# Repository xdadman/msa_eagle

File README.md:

#MSA - Scotty's Modular Spectrum Analyzer Eagle Schematics and PCB Layouts
This repository contains Eagle schematics and PCB layouts for Scotty's MSA.

See http://scottyspectrumanalyzer.com/ website for detailed information how to build, calibrate, and operate the MSA. 

The files and in Eagle 7.1 format.

Most of the parts in the MSA library have defined Farnell order codes.
The rest are from Digikey and Minicircuits.

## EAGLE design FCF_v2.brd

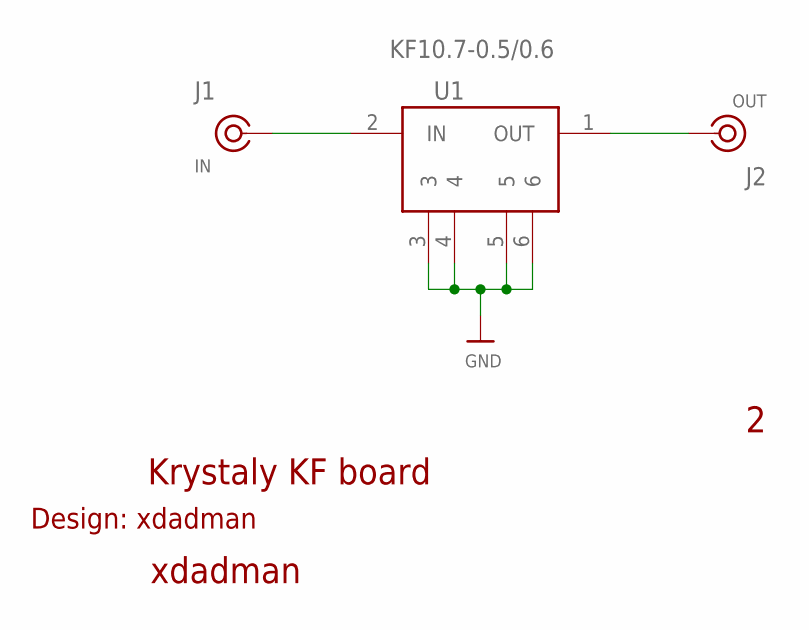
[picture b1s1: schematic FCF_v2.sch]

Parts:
J1: IN; SLIM_COAX_PAD
J2: OUT; SLIM_COAX_PAD
U1: KF10.7-0.5/0.6; KF-17

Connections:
GND: J1.GND, J2.GND, U1.3, U1.4, U1.5, U1.6
unnamed: J1.SIG (1), U1.2 (IN)
unnamed: J2.SIG (1), U1.1 (OUT)

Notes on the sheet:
xdadman
Krystaly KF board
Design: xdadman

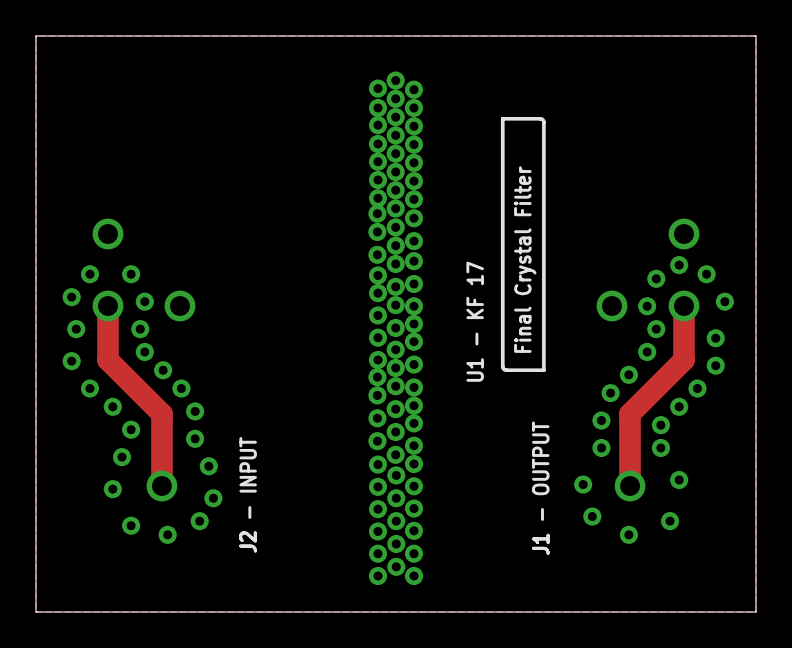
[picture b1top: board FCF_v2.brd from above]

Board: 2 copper layers, 40.0 x 32.0 mm, 3 parts (1 on the bottom side), 3 nets.

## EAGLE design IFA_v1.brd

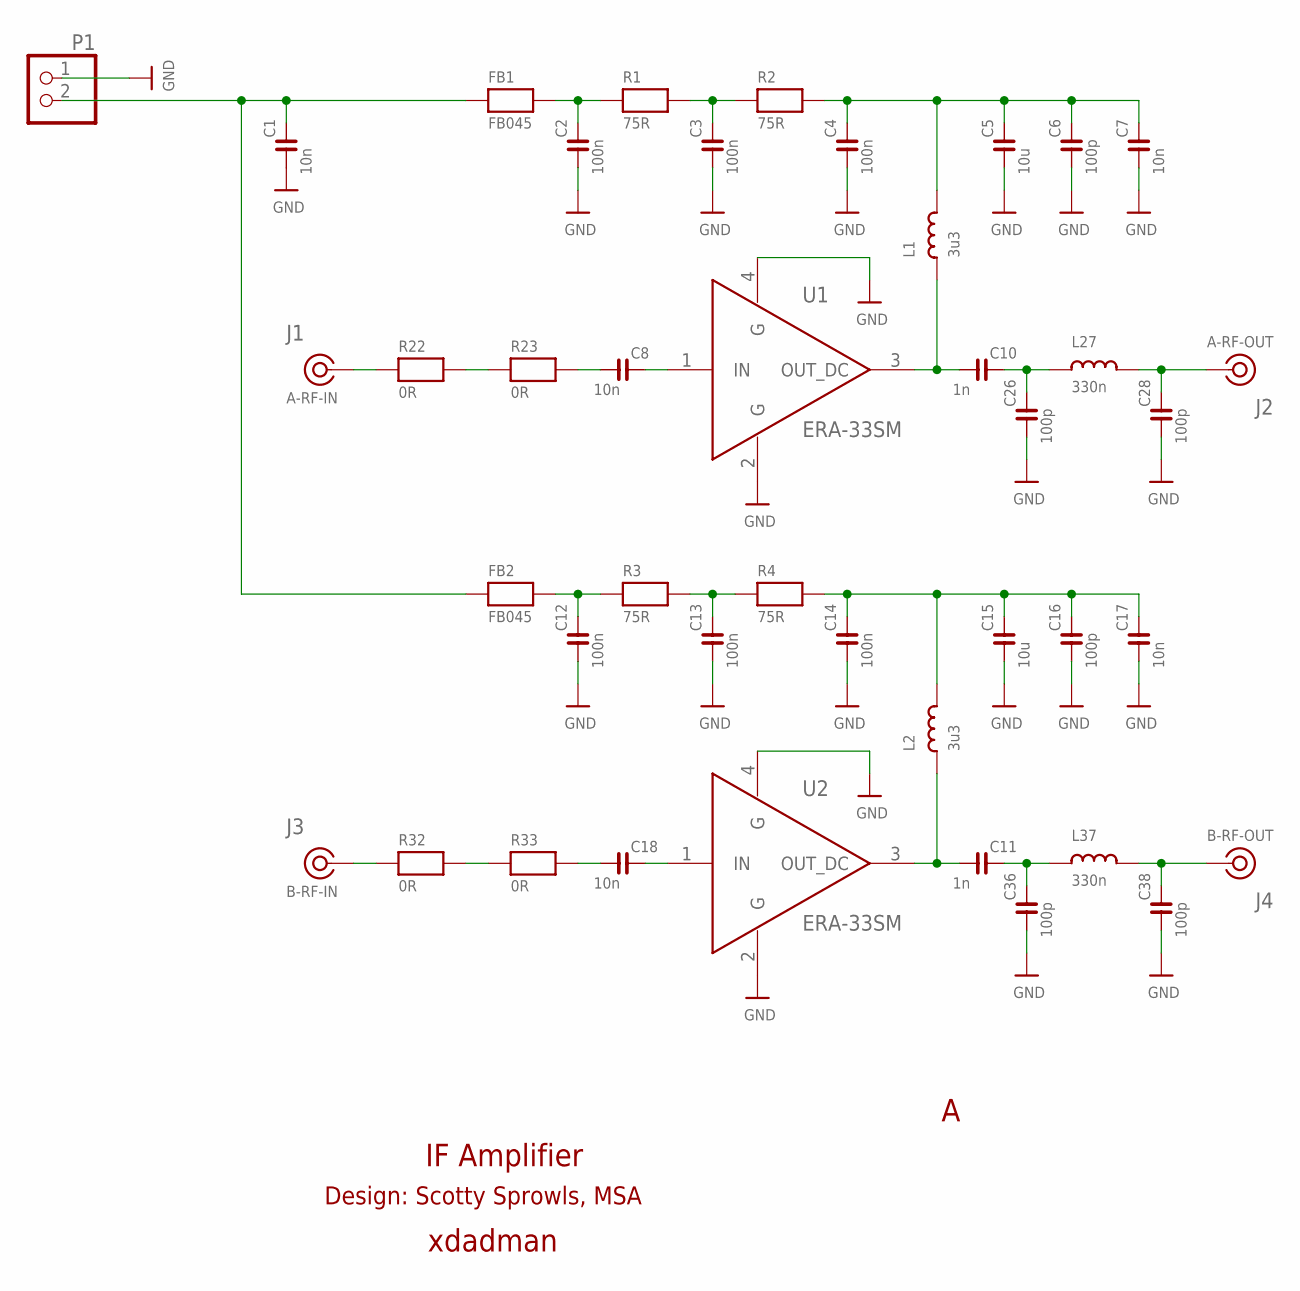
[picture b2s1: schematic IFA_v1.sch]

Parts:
C1, C7, C8, C17, C18: 10n; C0805
C2, C3, C4, C12, C13, C14: 100n; C0805
C5, C15: 10u; C1206
C6, C16, C26, C28, C36, C38: 100p; C0805
C10, C11: 1n; C0805
FB1, FB2: FB045; R0805
J1: A-RF-IN; SLIM_COAX_PAD
J2: A-RF-OUT; SLIM_COAX_PAD
J3: B-RF-IN; SLIM_COAX_PAD
J4: B-RF-OUT; SLIM_COAX_PAD
L1, L2: 3u3; L805
L27, L37: 330n; L805
P1: PINHD-1X2; 1X02
R1, R2, R3, R4: 75R; R0805
R22, R23, R32, R33: 0R; R0805
U1, U2: ERA-33SM; WW107

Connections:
GND: C1.1, C2.1, C3.1, C4.1, C5.1, C6.1, C7.1, C12.1, C13.1, C14.1, C15.1, C16.1, C17.1, C26.1, C28.1, C36.1, C38.1, J1.GND, J2.GND, J3.GND, J4.GND, P1.1, U1.2 (G), U1.4 (G), U2.2 (G), U2.4 (G)
unnamed: C2.2, FB1.2, R1.1
unnamed: C1.2, FB1.1, FB2.1, P1.2
unnamed: C3.2, R1.2, R2.1
unnamed: J1.SIG (1), R22.1
unnamed: C4.2, C5.2, C6.2, C7.2, L1.2, R2.2
unnamed: R22.2, R23.1
unnamed: C8.1, R23.2
unnamed: C8.2, U1.1 (IN)
unnamed: C28.2, J2.SIG (1), L27.2
unnamed: C10.1, L1.1, U1.3 (OUT_DC)
unnamed: C10.2, C26.2, L27.1
unnamed: C12.2, FB2.2, R3.1
unnamed: C13.2, R3.2, R4.1
unnamed: C14.2, C15.2, C16.2, C17.2, L2.2, R4.2
unnamed: J3.SIG (1), R32.1
unnamed: R32.2, R33.1
unnamed: C18.1, R33.2
unnamed: C18.2, U2.1 (IN)
unnamed: C11.1, L2.1, U2.3 (OUT_DC)
unnamed: C11.2, C36.2, L37.1
unnamed: C38.2, J4.SIG (1), L37.2

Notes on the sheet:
xdadman
IF Amplifier
Design: Scotty Sprowls, MSA

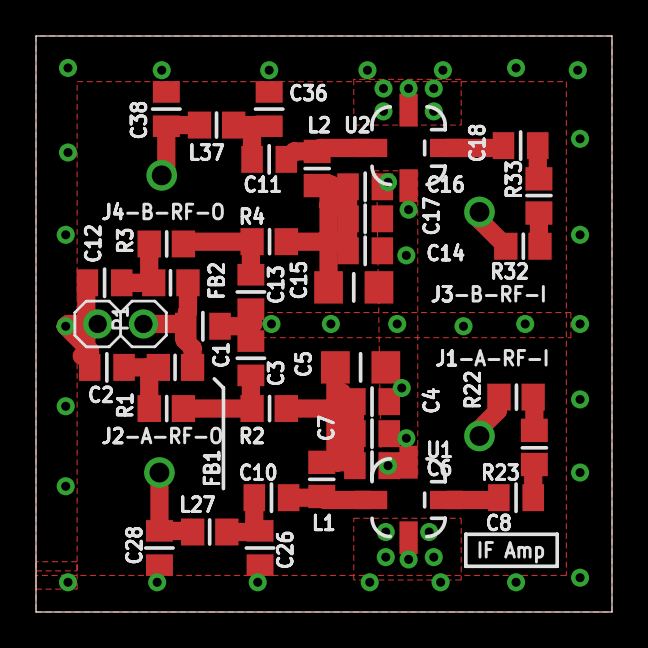
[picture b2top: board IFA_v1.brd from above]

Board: 2 copper layers, 32.0 x 32.0 mm, 42 parts (0 on the bottom side), 22 nets.

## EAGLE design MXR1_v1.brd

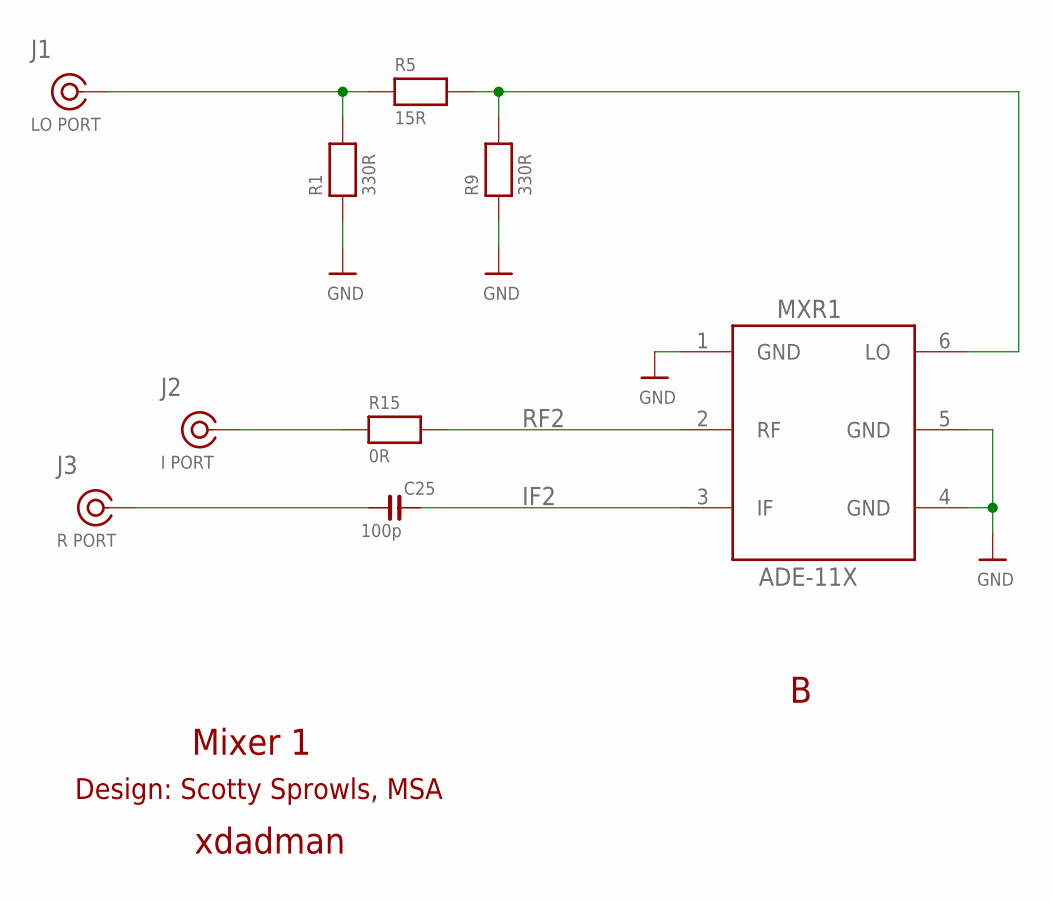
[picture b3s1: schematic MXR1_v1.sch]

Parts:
C25: 100p; C0805
J1: LO PORT; SLIM_COAX_PAD
J2: I PORT; SLIM_COAX_PAD
J3: R PORT; SLIM_COAX_PAD
MXR1: ADE-11X
R1, R9: 330R; R0805
R5: 15R; 0805
R15: 0R; R0805

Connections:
GND: J1.GND, J2.GND, J3.GND, MXR1.1 (GND), MXR1.4 (GND), MXR1.5 (GND), R1.1, R9.1
IF: C25.1, J3.SIG (1)
IF2: C25.2, MXR1.3 (IF)
LO: J1.SIG (1), R1.2, R5.1
LO3: MXR1.6 (LO), R5.2, R9.2
RF: J2.SIG (1), R15.1
RF2: MXR1.2 (RF), R15.2

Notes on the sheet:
xdadman
Mixer 1
Design: Scotty Sprowls, MSA

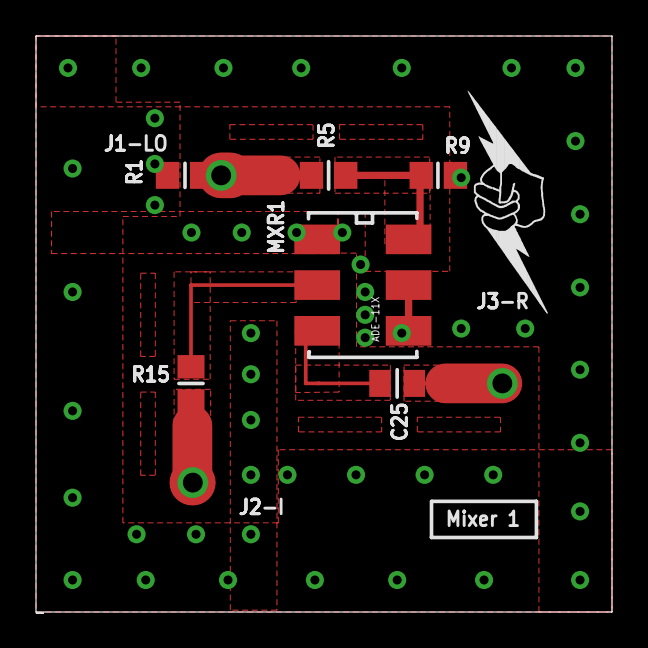
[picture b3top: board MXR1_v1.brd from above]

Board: 2 copper layers, 32.0 x 32.0 mm, 9 parts (0 on the bottom side), 7 nets.

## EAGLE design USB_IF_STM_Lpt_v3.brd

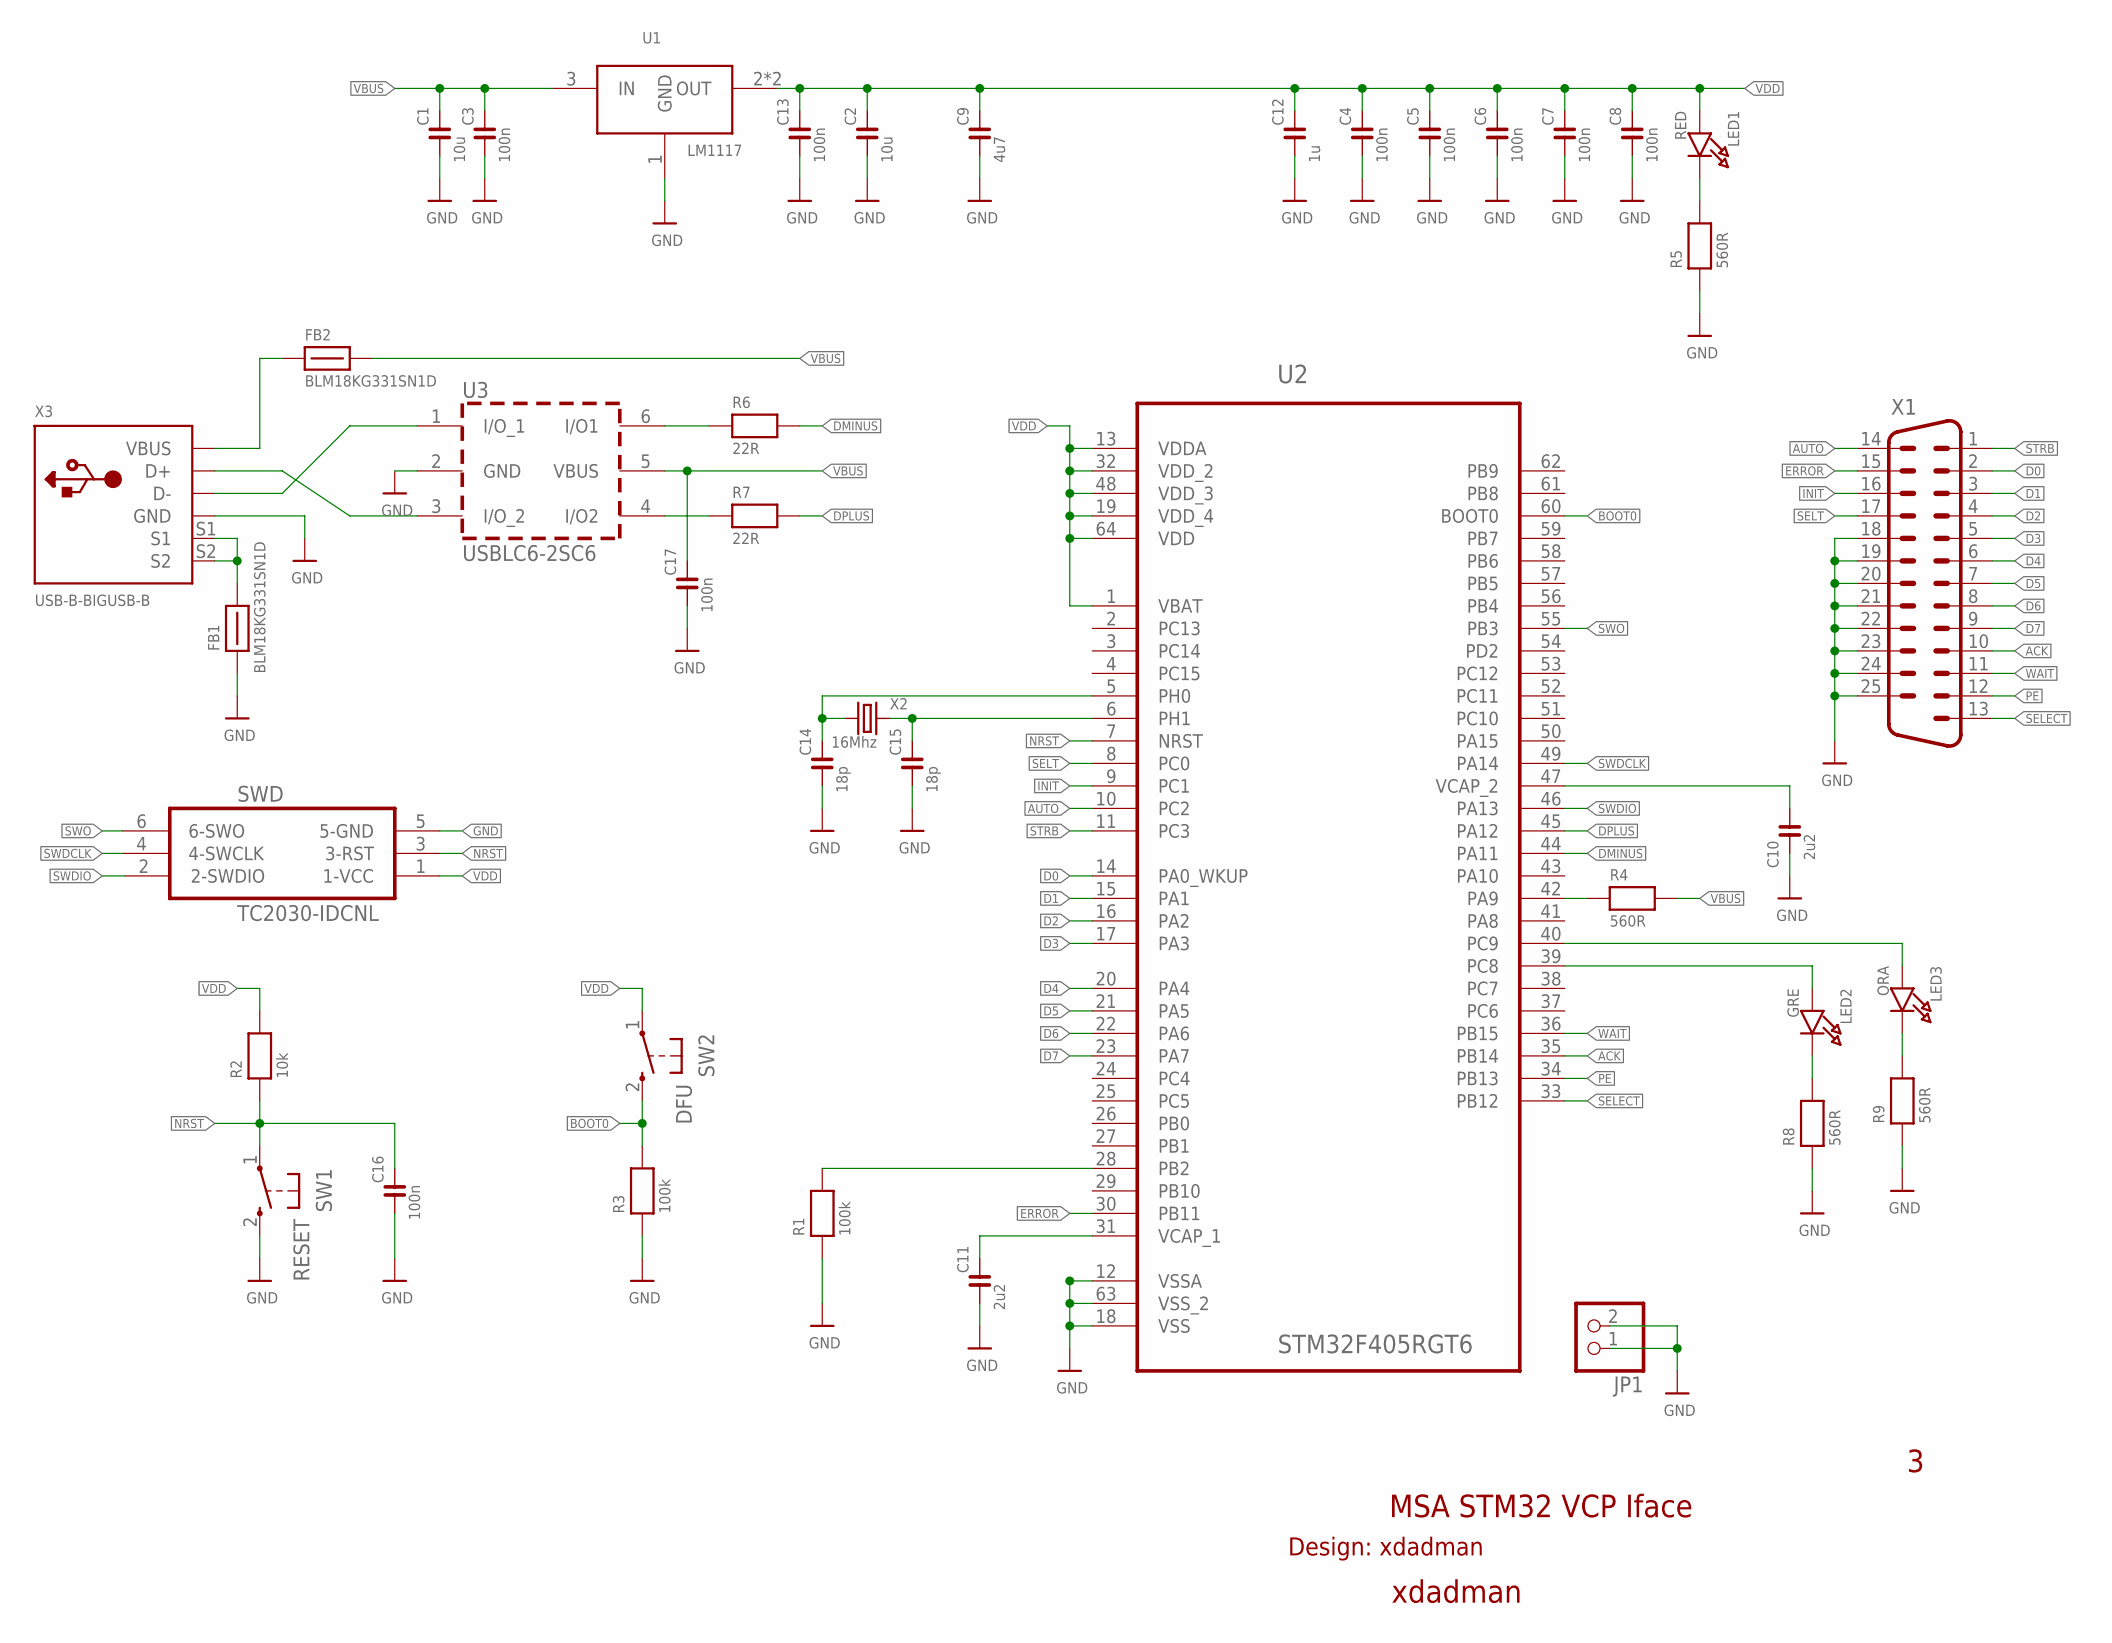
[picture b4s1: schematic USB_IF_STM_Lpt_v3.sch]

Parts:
C1, C2: 10u; C1206
C3, C4, C5, C6, C7, C8, C13, C16, C17: 100n; C0603
C9: 4u7; C0603
C10, C11: 2u2; C0603
C12: 1u; C0603
C14, C15: 18p; C0603
FB1, FB2: BLM18KG331SN1D; R0603
JP1: PINHD-1X2; 1X02
LED1: RED; CHIPLED_0603
LED2: GRE; CHIPLED_0603
LED3: ORA; CHIPLED_0603
R1, R3: 100k; R0603
R2: 10k; 0603-MINI
R4, R5, R8, R9: 560R; R0603
R6, R7: 22R; R0603
SW1: RESET; TACTILE_6X3
SW2: DFU; TACTILE_6X3
SWD: TC2030-IDCNL; TC2030-IDC-NL
U1: LM1117; SOT223
U2: STM32F405RGT6; QFP50P1200X1200X160-64N
U3: USBLC6-2SC6; SOT-23-6L
X1: M25D
X2: 16Mhz; ABRACON_ABM7
X3: USB-B-BIGUSB-B; USB-B-PTH

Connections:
ACK: U2.35 (PB14), X1.10
AUTO: U2.10 (PC2), X1.14
BOOT0: R3.2, SW2.2, U2.60 (BOOT0)
D0: U2.14 (PA0_WKUP), X1.2
D1: U2.15 (PA1), X1.3
D2: U2.16 (PA2), X1.4
D3: U2.17 (PA3), X1.5
D4: U2.20 (PA4), X1.6
D5: U2.21 (PA5), X1.7
D6: U2.22 (PA6), X1.8
D7: U2.23 (PA7), X1.9
DMINUS: R6.2, U2.44 (PA11)
DPLUS: R7.2, U2.45 (PA12)
ERROR: U2.30 (PB11), X1.15
GND: C1.1, C2.1, C3.1, C4.1, C5.1, C6.1, C7.1, C8.1, C9.1, C10.1, C11.1, C12.1, C13.1, C14.1, C15.1, C16.1, C17.1, FB1.1, JP1.1, JP1.2, R1.1, R3.1, R5.1, R8.1, R9.1, SW1.2, SWD.5 (5-GND), U1.1 (GND), U2.12 (VSSA), U2.18 (VSS), U2.63 (VSS_2), U3.2 (GND), X1.18, X1.19, X1.20, X1.21, X1.22, X1.23, X1.24, X1.25, X3.GND
INIT: U2.9 (PC1), X1.16
unnamed: R1.2, U2.28 (PB2)
unnamed: R4.1, U2.42 (PA9)
unnamed: LED1.C, R5.2
unnamed: C11.2, U2.31 (VCAP_1)
unnamed: C15.2, U2.6 (PH1), X2.P$2 (2)
unnamed: C14.2, U2.5 (PH0), X2.P$1 (1)
unnamed: FB1.2, X3.S1, X3.S2
unnamed: FB2.1, X3.VBUS
unnamed: U3.3 (I/O_2), X3.D+
unnamed: U3.1 (I/O_1), X3.D-
unnamed: R6.1, U3.6 (I/O1)
unnamed: R7.1, U3.4 (I/O2)
unnamed: C10.2, U2.47 (VCAP_2)
unnamed: LED2.C, R8.2
unnamed: LED3.C, R9.2
NRST: C16.2, R2.1, SW1.1, SWD.3 (3-RST), U2.7 (NRST)
PE: U2.34 (PB13), X1.12
SELECT: U2.33 (PB12), X1.13
SELT: U2.8 (PC0), X1.17
STRB: U2.11 (PC3), X1.1
SWDCLK: SWD.4 (4-SWCLK), U2.49 (PA14)
SWDIO: SWD.2 (2-SWDIO), U2.46 (PA13)
SWO: SWD.6 (6-SWO), U2.55 (PB3)
VBUS: C1.2, C3.2, C17.2, FB2.2, R4.2, U1.3 (IN), U3.5 (VBUS)
VDD: C2.2, C4.2, C5.2, C6.2, C7.2, C8.2, C9.2, C12.2, C13.2, LED1.A, R2.2, SW2.1, SWD.1 (1-VCC), U1.2 (OUT), U1.4 (OUT), U2.1 (VBAT), U2.13 (VDDA), U2.19 (VDD_4), U2.32 (VDD_2), U2.48 (VDD_3), U2.64 (VDD)
VDD1: LED2.A, U2.39 (PC8)
VDD2: LED3.A, U2.40 (PC9)
WAIT: U2.36 (PB15), X1.11

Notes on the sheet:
xdadman
MSA STM32 VCP Iface
Design: xdadman

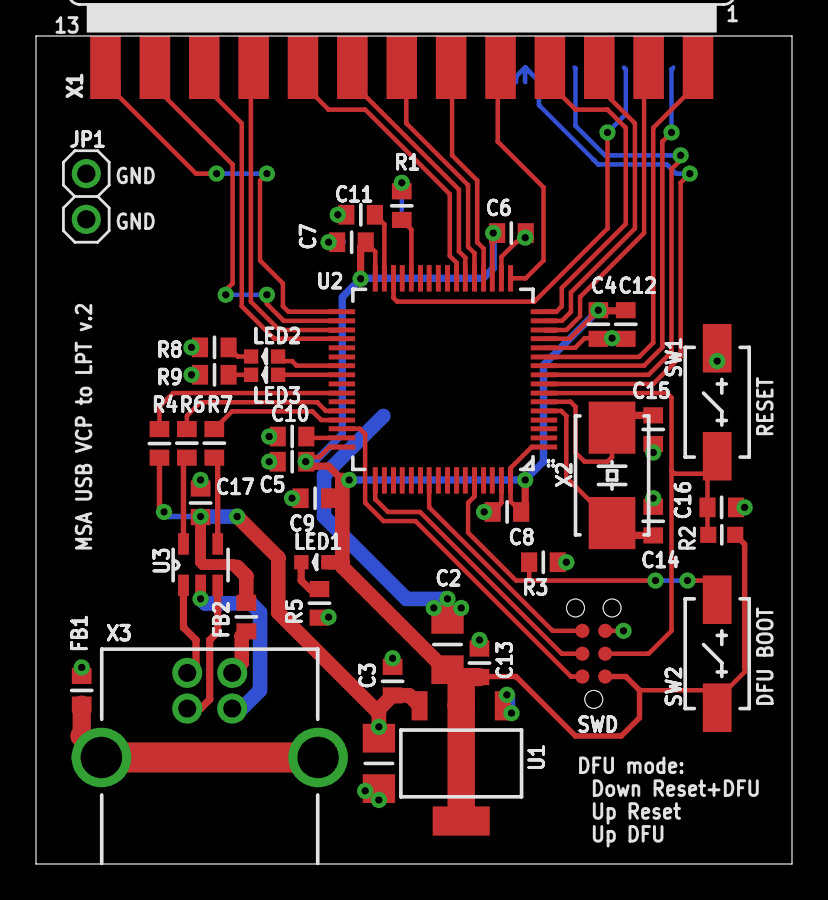
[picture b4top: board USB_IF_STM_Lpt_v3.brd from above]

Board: 2 copper layers, 42.0 x 46.0 mm, 41 parts (0 on the bottom side), 44 nets.

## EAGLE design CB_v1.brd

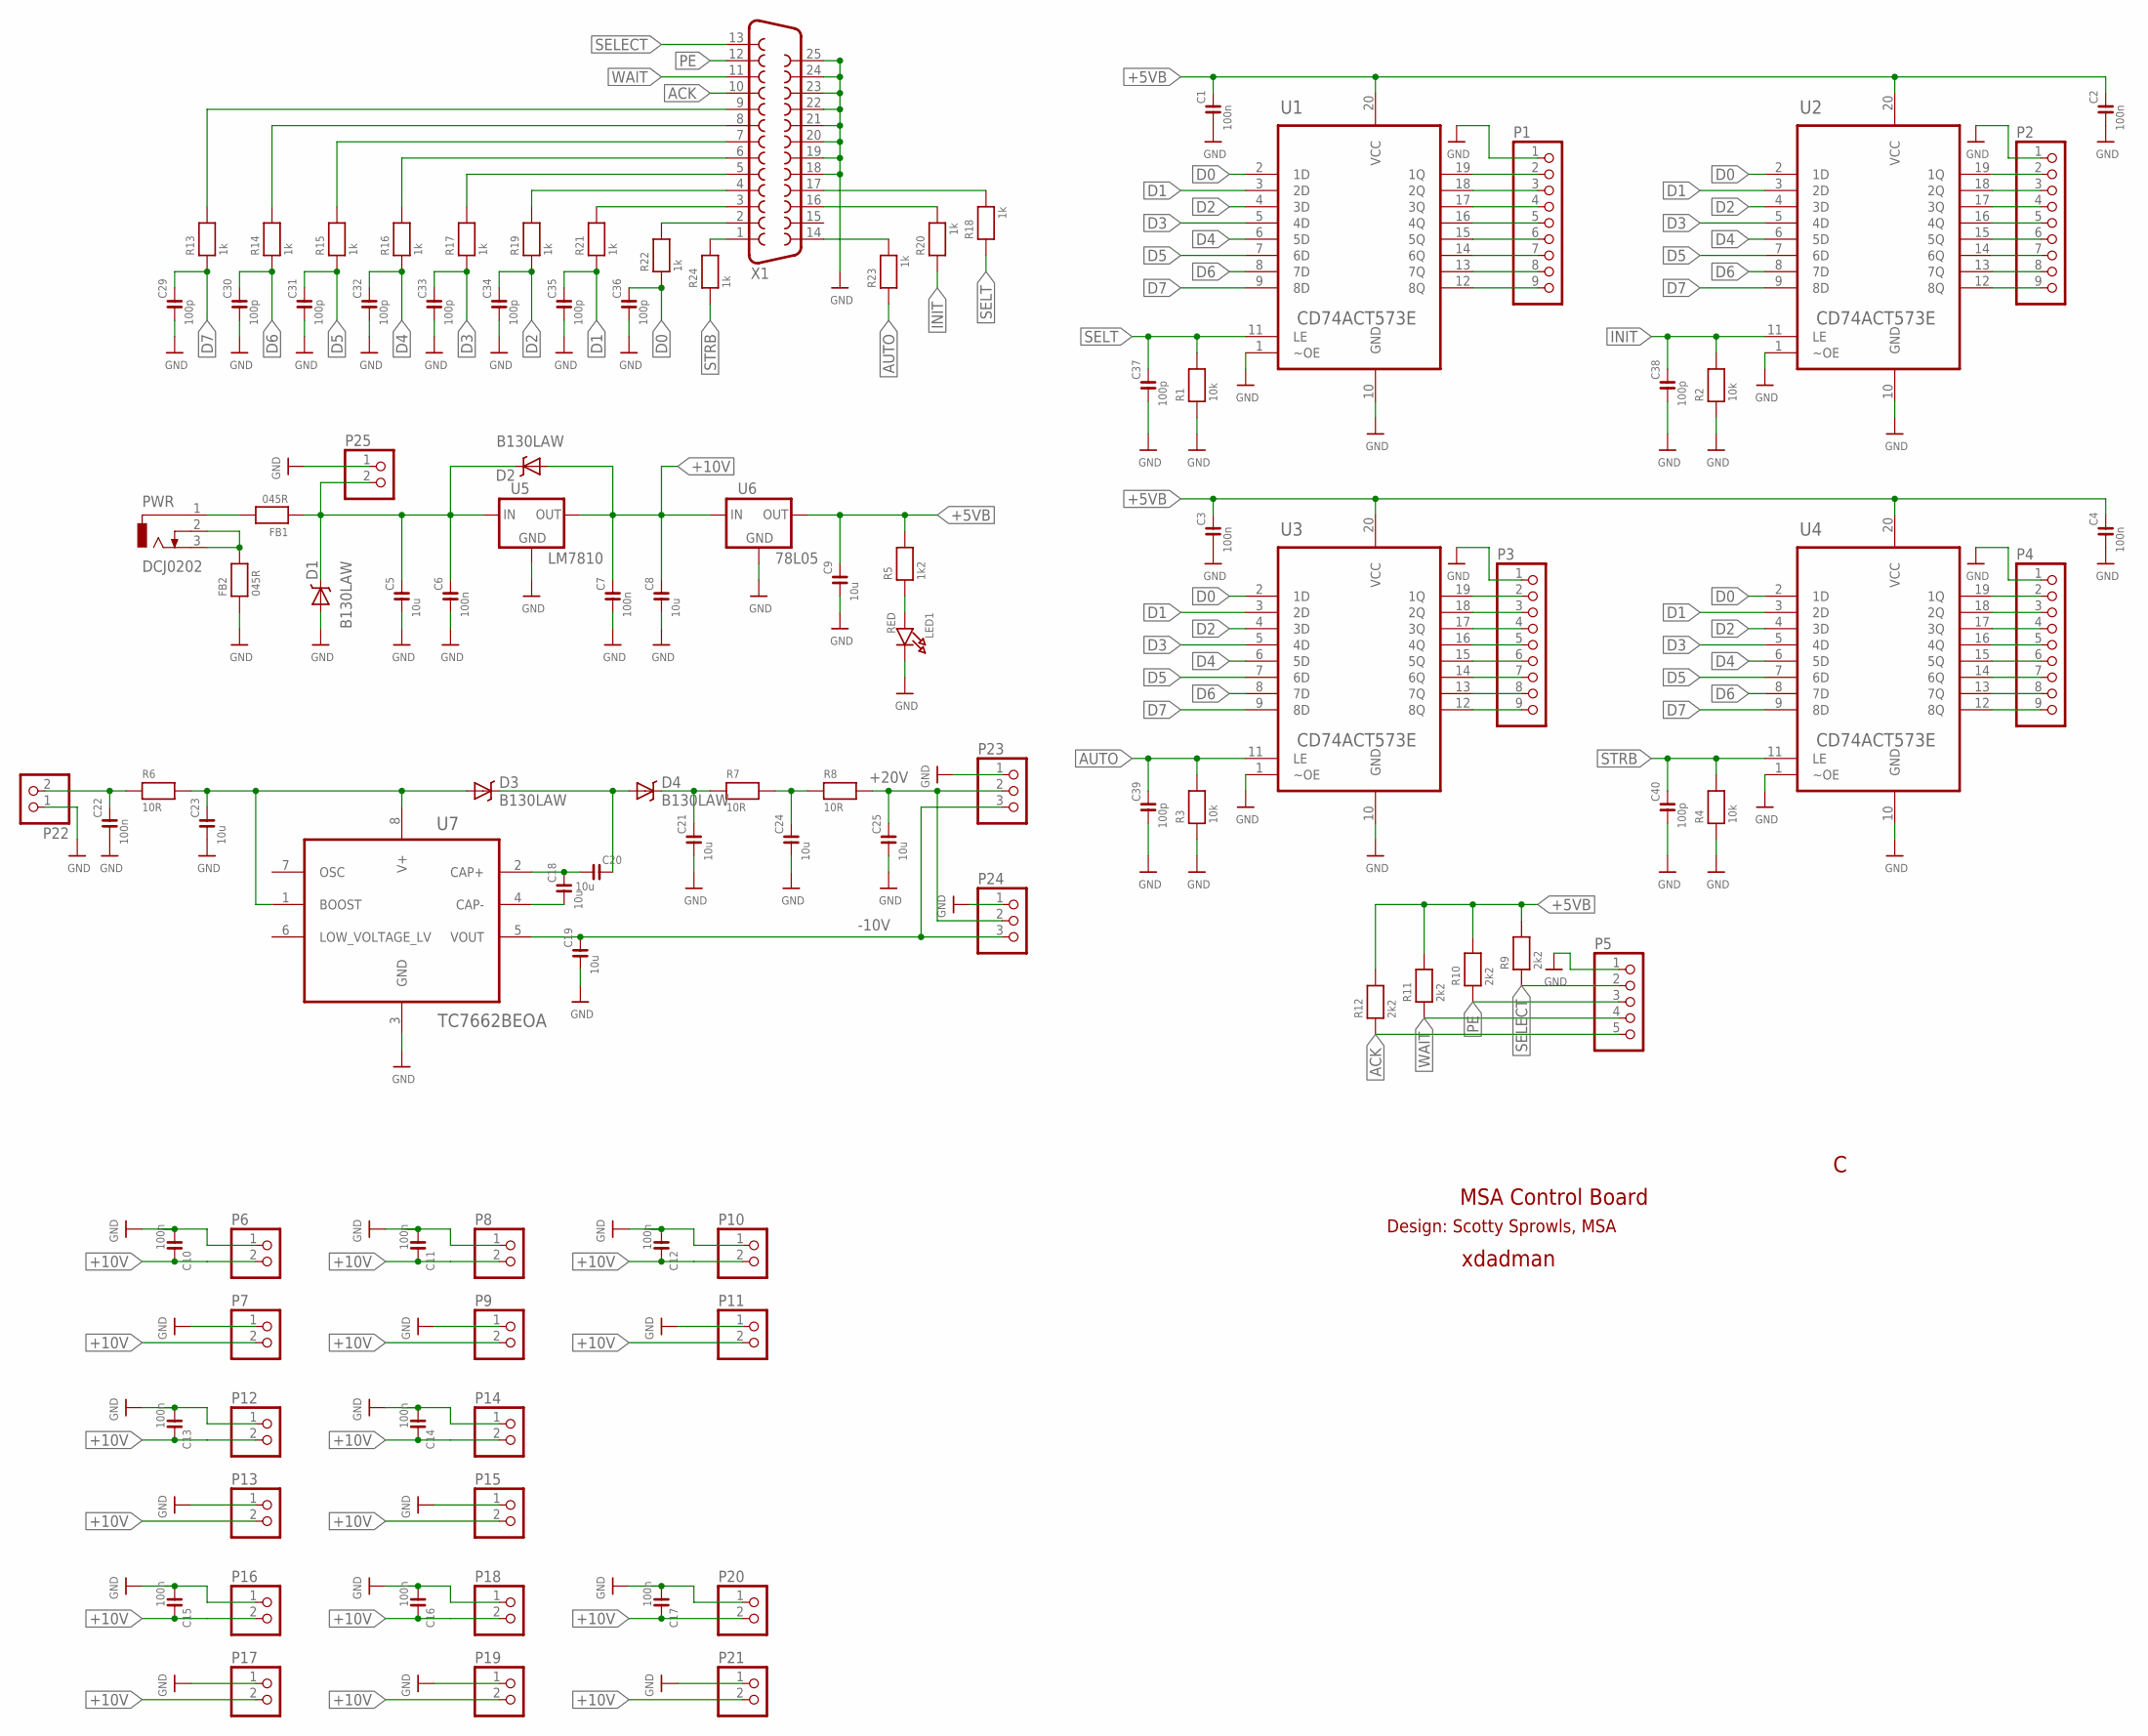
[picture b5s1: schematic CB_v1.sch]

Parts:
C1, C2, C3, C4, C6, C7, C10, C11, C12, C13, C14, C15, C16, C17, C22: 100n; C0805
C5, C8, C9, C18, C19, C20, C21, C23, C24, C25: 10u; C1206
C29, C30, C31, C32, C33, C34, C35, C36, C37, C38, C39, C40: 100p; C0805
D1, D2, D3, D4: B130LAW; SOD-123
FB1, FB2: 045R; R0805
LED1: RED; CHIPLED_0603
P1, P2, P3, P4: PINHD-1X9; 1X09ROUND
P5: PINHD-1X5; 1X05
P6, P7, P8, P9, P10, P11, P12, P13, P14, P15, P16, P17, P18, P19, P20, P21, P22, P25: PINHD-1X2; 1X02
P23, P24: PINHD-1X3; 1X03
PWR: DCJ0202
R1, R2, R3, R4: 10k; R0805
R5: 1k2; R0805
R6, R7, R8: 10R; R0805
R9, R10, R11, R12: 2k2; R0805
R13, R14, R15, R16, R17, R18, R19, R20, R21, R22, R23, R24: 1k; R0805
U1, U2, U3, U4: CD74ACT573E; DIP254P762X508-20
U5: LM7810; TO220V
U6: 78L05; SOT89
U7: TC7662BEOA; SOIC127P600X175-8N_JDA
X1: F25D

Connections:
+5VB: C1.2, C2.2, C3.2, C4.2, C9.2, R5.2, R9.2, R10.2, R11.2, R12.2, U1.20 (VCC), U2.20 (VCC), U3.20 (VCC), U4.20 (VCC), U6.1 (OUT)
+10V: C7.2, C8.2, C10.2, C11.2, C12.2, C13.2, C14.2, C15.2, C16.2, C17.2, D2.A, P6.2, P7.2, P8.2, P9.2, P10.2, P11.2, P12.2, P13.2, P14.2, P15.2, P16.2, P17.2, P18.2, P19.2, P20.2, P21.2, U5.3 (OUT), U6.3 (IN)
+20V: C25.2, P23.2, P24.2, R8.2
-10V: C19.2, P23.3, P24.3, U7.5 (VOUT)
ACK: P5.5, R12.1, X1.10
AUTO: C39.2, R3.2, R23.2, U3.11 (LE)
D0: C36.2, R22.1, U1.2 (1D), U2.2 (1D), U3.2 (1D), U4.2 (1D)
D1: C35.2, R21.1, U1.3 (2D), U2.3 (2D), U3.3 (2D), U4.3 (2D)
D2: C34.2, R19.1, U1.4 (3D), U2.4 (3D), U3.4 (3D), U4.4 (3D)
D3: C33.2, R17.1, U1.5 (4D), U2.5 (4D), U3.5 (4D), U4.5 (4D)
D4: C32.2, R16.1, U1.6 (5D), U2.6 (5D), U3.6 (5D), U4.6 (5D)
D5: C31.2, R15.1, U1.7 (6D), U2.7 (6D), U3.7 (6D), U4.7 (6D)
D6: C30.2, R14.1, U1.8 (7D), U2.8 (7D), U3.8 (7D), U4.8 (7D)
D7: C29.2, R13.1, U1.9 (8D), U2.9 (8D), U3.9 (8D), U4.9 (8D)
GND: C1.1, C2.1, C3.1, C4.1, C5.1, C6.1, C7.1, C8.1, C9.1, C10.1, C11.1, C12.1, C13.1, C14.1, C15.1, C16.1, C17.1, C19.1, C21.1, C22.1, C23.1, C24.1, C25.1, C29.1, C30.1, C31.1, C32.1, C33.1, C34.1, C35.1, C36.1, C37.1, C38.1, C39.1, C40.1, D1.A, FB2.1, LED1.C, P1.1, P2.1, P3.1, P4.1, P5.1, P6.1, P7.1, P8.1, P9.1, P10.1, P11.1, P12.1, P13.1, P14.1, P15.1, P16.1, P17.1, P18.1, P19.1, P20.1, P21.1, P22.1, P23.1, P24.1, P25.1, R1.1, R2.1, R3.1, R4.1, U1.1 (~OE), U1.10 (GND), U2.1 (~OE), U2.10 (GND), U3.1 (~OE), U3.10 (GND), U4.1 (~OE), U4.10 (GND), U5.2 (GND), U6.2 (GND), U6.4 (GND), U7.3 (GND), X1.18, X1.19, X1.20, X1.21, X1.22, X1.23, X1.24, X1.25
INIT: C38.2, R2.2, R20.2, U2.11 (LE)
unnamed: P1.2, U1.19 (1Q)
unnamed: P3.2, U3.19 (1Q)
unnamed: P2.2, U2.19 (1Q)
unnamed: P4.2, U4.19 (1Q)
unnamed: R22.2, X1.2
unnamed: R18.1, X1.17
unnamed: R21.2, X1.3
unnamed: R19.2, X1.4
unnamed: R13.2, X1.9
unnamed: R23.1, X1.14
unnamed: R20.1, X1.16
unnamed: R14.2, X1.8
unnamed: R15.2, X1.7
unnamed: R16.2, X1.6
unnamed: R17.2, X1.5
unnamed: FB1.2, PWR.1
unnamed: P1.3, U1.18 (2Q)
unnamed: P1.4, U1.17 (3Q)
unnamed: R24.2, X1.1
unnamed: FB2.2, PWR.2, PWR.3
unnamed: C5.2, C6.2, D1.C, D2.C, FB1.1, P25.2, U5.1 (IN)
unnamed: LED1.A, R5.1
unnamed: C23.2, D3.A, R6.2, U7.1 (BOOST), U7.8 (V+)
unnamed: C22.2, P22.2, R6.1
unnamed: C20.2, D3.C, D4.A
unnamed: C21.2, D4.C, R7.1
unnamed: P1.5, U1.16 (4Q)
unnamed: C18.1, U7.4 (CAP-)
unnamed: C18.2, C20.1, U7.2 (CAP+)
unnamed: C24.2, R7.2, R8.1
unnamed: P1.6, U1.15 (5Q)
unnamed: P1.7, U1.14 (6Q)
unnamed: P1.8, U1.13 (7Q)
unnamed: P1.9, U1.12 (8Q)
unnamed: P2.3, U2.18 (2Q)
unnamed: P2.4, U2.17 (3Q)
unnamed: P2.5, U2.16 (4Q)
unnamed: P2.6, U2.15 (5Q)
unnamed: P2.7, U2.14 (6Q)
unnamed: P2.8, U2.13 (7Q)
unnamed: P2.9, U2.12 (8Q)
unnamed: P3.3, U3.18 (2Q)
unnamed: P3.4, U3.17 (3Q)
unnamed: P3.5, U3.16 (4Q)
unnamed: P3.6, U3.15 (5Q)
unnamed: P3.7, U3.14 (6Q)
unnamed: P3.8, U3.13 (7Q)
unnamed: P3.9, U3.12 (8Q)
unnamed: P4.3, U4.18 (2Q)
unnamed: P4.4, U4.17 (3Q)
unnamed: P4.5, U4.16 (4Q)
unnamed: P4.6, U4.15 (5Q)
unnamed: P4.7, U4.14 (6Q)
unnamed: P4.8, U4.13 (7Q)
unnamed: P4.9, U4.12 (8Q)
PE: P5.3, R10.1, X1.12
SELECT: P5.2, R9.1, X1.13
SELT: C37.2, R1.2, R18.2, U1.11 (LE)
STRB: C40.2, R4.2, R24.1, U4.11 (LE)
WAIT: P5.4, R11.1, X1.11

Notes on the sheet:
xdadman
MSA Control Board
Design: Scotty Sprowls, MSA

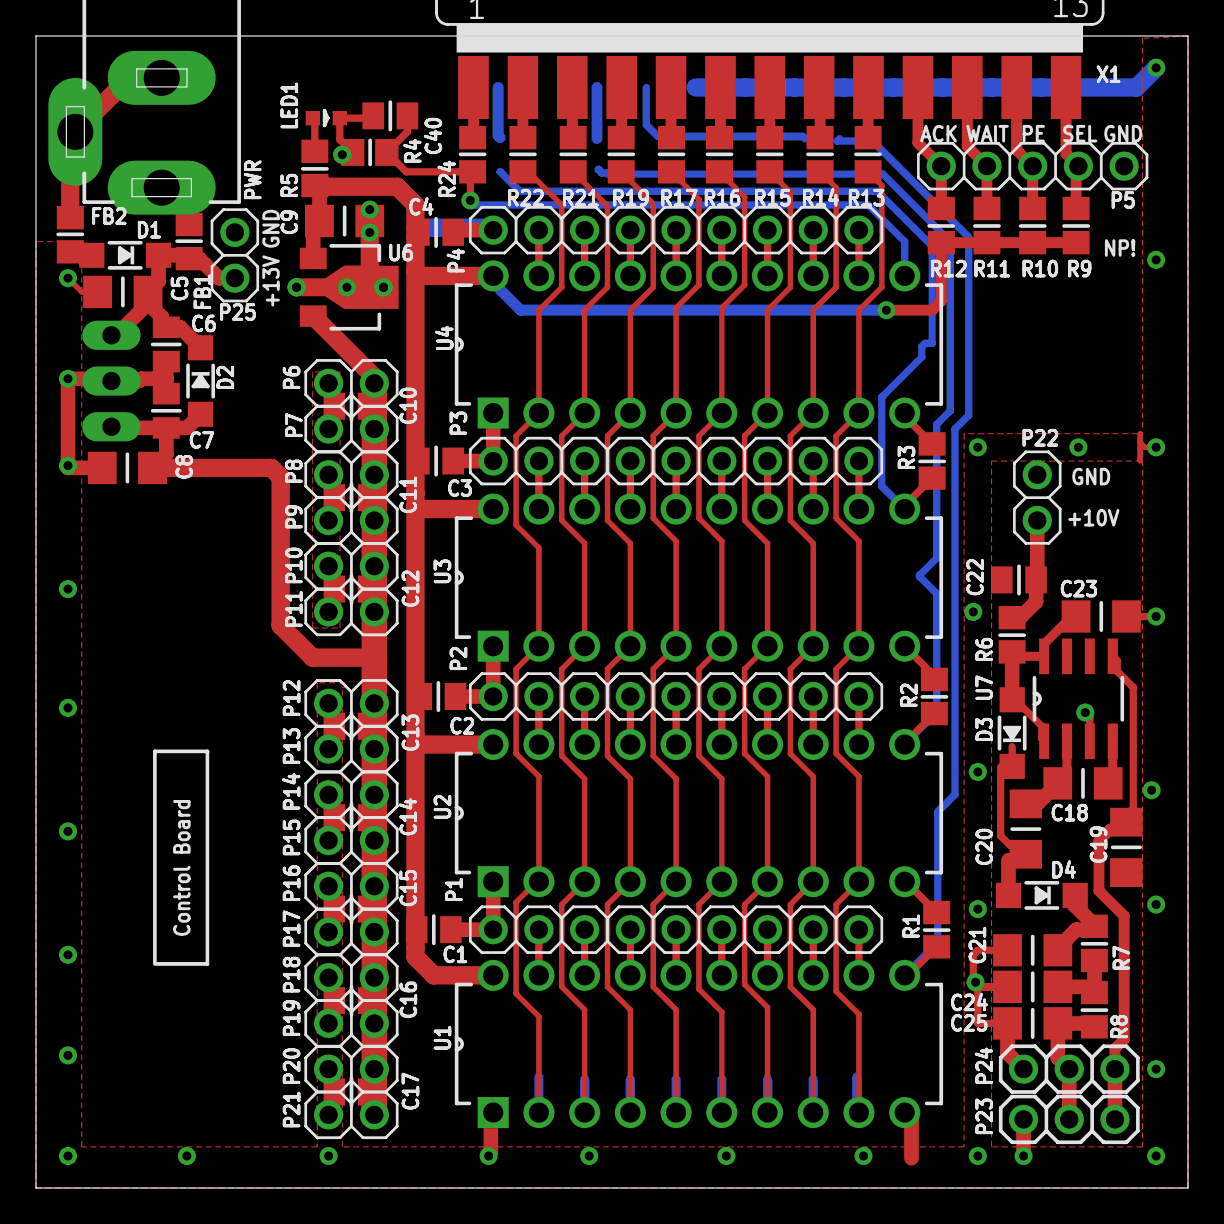
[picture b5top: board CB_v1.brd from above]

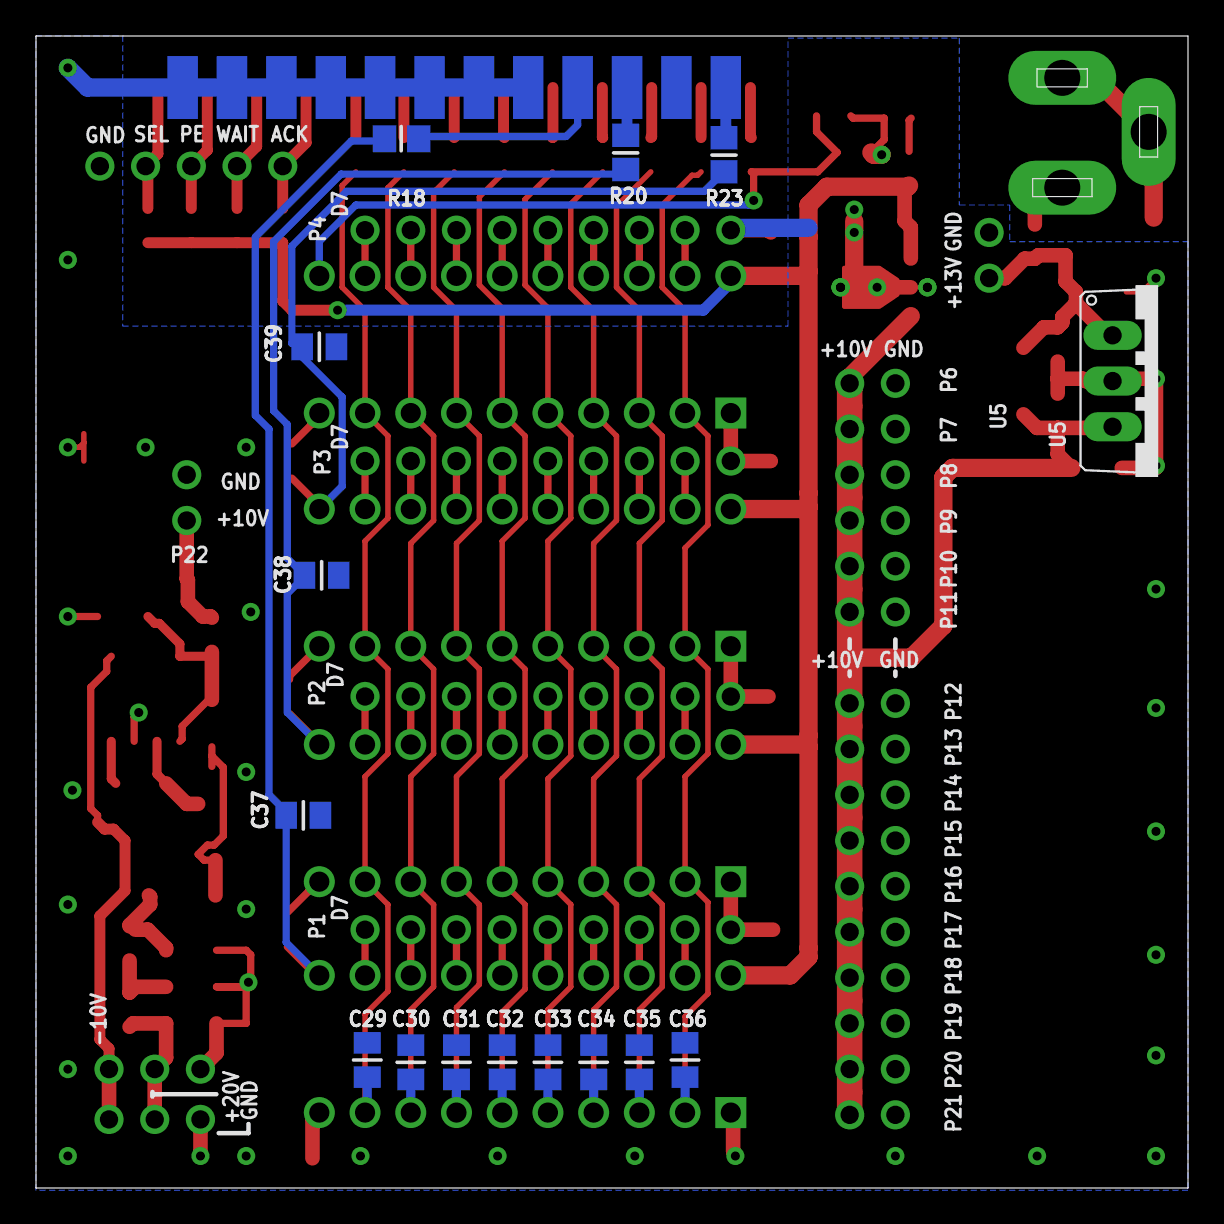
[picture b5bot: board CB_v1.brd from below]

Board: 2 copper layers, 64.0 x 64.0 mm, 102 parts (15 on the bottom side), 76 nets.

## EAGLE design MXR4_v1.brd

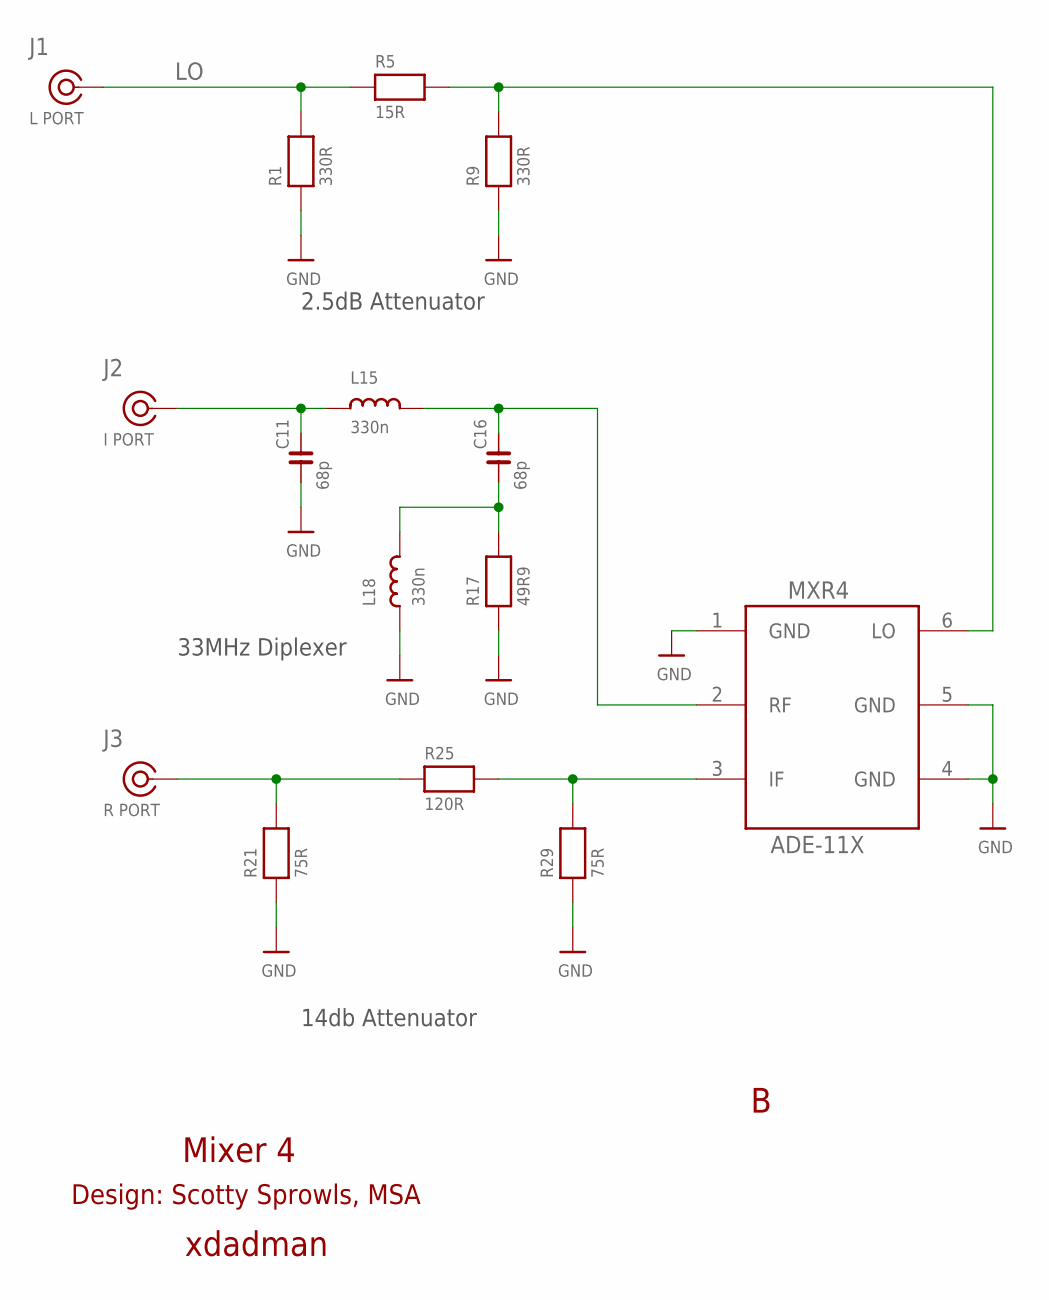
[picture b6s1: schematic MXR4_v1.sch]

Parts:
C11, C16: 68p; C0805
J1: L PORT; SLIM_COAX_PAD
J2: I PORT; SLIM_COAX_PAD
J3: R PORT; SLIM_COAX_PAD
L15, L18: 330n; L805
MXR4: ADE-11X
R1, R9: 330R; R0805
R5: 15R; 0805
R17: 49R9; R0805
R21, R29: 75R; R0805
R25: 120R; R0805

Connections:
GND: C11.1, J1.GND, J2.GND, J3.GND, L18.1, MXR4.1 (GND), MXR4.4 (GND), MXR4.5 (GND), R1.1, R9.1, R17.1, R21.1, R29.1
IF: J3.SIG (1), R21.2, R25.1
IF2: MXR4.3 (IF), R25.2, R29.2
LO: J1.SIG (1), R1.2, R5.1
LO3: MXR4.6 (LO), R5.2, R9.2
unnamed: C16.1, L18.2, R17.2
RF: C11.2, J2.SIG (1), L15.1
RF2: C16.2, L15.2, MXR4.2 (RF)

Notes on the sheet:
14db Attenuator
33MHz Diplexer
2.5dB Attenuator
xdadman
Mixer 4
Design: Scotty Sprowls, MSA
